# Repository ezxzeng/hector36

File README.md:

# Hector36
## A sub-100×100 mm split keyboard inspired by Totem, without the extra pinky key

left | right | outline
-|-|-
 |  | 

Hector36 is a 36-key split keyboard with a 5×3 layout and 3 thumb keys per half.  
It is designed to stay under **100 mm × 100 mm per PCB**, which makes fabrication much cheaper while still keeping a comfortable, aggressively staggered and splayed layout.

## Features
- Sub-100×100 mm PCB for low fabrication cost
- Split 36-key layout with 3 thumb keys per half
- Reversible PCB
- Diode-less design
- Programmatically generated with Ergogen
- hotswap sockets

## PCB variants

This repo currently contains several board variants:

| Version | Status | Folder | Buildguide |
|---|---|---|---|
| MX | Tested and working | [`routed_pcb/mx`](routed_pcb/mx) | [guide](routed_pcb/mx/README.md#Build-Guide)
| Choc with choc spacing | Fabricated, not yet received or tested | [`routed_pcb/choc_spacing`](routed_pcb/choc_spacing) | tbd
| Choc with mx spacing | Not routed | `routed_pcb/choc` | tbd
| Gateron low profile with mx spacing | Not routed | `routed_pcb/gateron_lp` | tbd

For PCB fabrication through JLCPCB or PCBWay, use the gerbers.zip file inside the corresponding version folder.

## Components

| Part                           | Qty |      Estimated price | Notes                                                          |
| ------------------------------ | --: | -------------------: | -------------------------------------------------------------- |
| PCB                            |   2 |          $3.50 for 5 |                                                                |
| nice!nano or nRF52840          |   2 | $4 each for nRF52840 |  I'm using nRF52840 for cheaper cost |
| Reset switch                   |   2 |        $3.40 for 100 | 3×6×2.5 mm, 2-pin, SMD push button                             |
| Power switch                   |   2 |           $4 for 100 | 7-pin, MSK 12C02                                               |
| Battery                        |   2 |            $15 for 2 | 301230, 3.7 V Li-Po                                            |
| 2P ST PH2.0 right-angle socket |   2 |           $2 for 100 | Optional                                                       |
| Hotswap socket                 |  36 |           $10 for 70 |     also depends on socket type    |
| Switch                         |  36 |                    — |                                                                |
| Keycap                         |  36 |                    — | Some keycaps may need rotated orientation for the Choc version. |
| M3 heat-set insert             |   8 |            $3 for 50 |                                                                |
| M3 screw                       |   8 |            $3 for 50 |                                                                |
| Rubber feet                    |   8 |            $5 for 50 |                                                                |

note that estimated price is from a brief look at aliexpress, and might be higher than what you'll actually have to pay if you buy in higher quantities (especially for batteries)

optional: [socketing the controller](https://docs.splitkb.com/frequently-asked-questions/about-split-keyboards/microcontrollers/sockets), see [this guide](https://www.40percent.club/p/socketing-pro-micro.html) or [this guide](https://docs.splitkb.com/product-guides/aurora-series/build-guide/microcontrollers)

## Firmware
see [zmk module](https://github.com/ezxzeng/zmk-keyboards-hector36)

## Inspiration

- [bgkeeb](https://github.com/sadekbaroudi/bgkeeb)
  - keyboard pcbs under 100mm x 100mm are cheap
- [cheapis](https://github.com/dotleon/cheapis) 
  - sweeps can be rotated for more room and length between the thumb cluster and rest of the keys and still fit within 100mm x 100mm
- [samoklava](https://github.com/soundmonster/samoklava) and [ergogen](https://ergogen.cache.works/) to get keyboard layouts programatically 
- [sweep](https://github.com/davidphilipbarr/Sweep) and [swweeep](https://github.com/sadekbaroudi/sweep36) for form factor and diode-less design
- [totem](https://github.com/GEIGEIGEIST/totem) and [KLOR](https://github.com/GEIGEIGEIST/KLOR)
  - keys layout
  - sandwich case looks really slick and clean, and can also hide the controller parts that will be located under the palm

## Other considerations
- this design does not support LEDs or displays
- [samoklava's](https://github.com/soundmonster/samoklava) auto routing does not really work here
- some keycaps might need to be rotated 90 degrees

## Rendering and generation

### Ergogen:
```bash
ergogen .
```
### Case:
printables: https://www.printables.com/model/1659997-case-for-hector36

onshape [link](https://cad.onshape.com/documents/dab7ead69061981322a5fa82/w/eeec2b07408bf6c3576b55db/e/49101eb28d1b1828dfaa91ca?renderMode=0&uiState=69ce0391edbfc1314134fd9e)

### Get board image renderings:
```bash
export pcb_type="mx"

docker run -v $(pwd):/kikit --entrypoint pcbdraw yaqwsx/kikit:v1.3.0-v7  plot --style style.json routed_pcb/$pcb_type/board.kicad_pcb routed_pcb/$pcb_type/images/board-front.png

docker run -v $(pwd):/kikit --entrypoint pcbdraw yaqwsx/kikit:v1.3.0-v7  plot --style style.json --side back routed_pcb/$pcb_type/board.kicad_pcb routed_pcb/$pcb_type/images/board-back.png
```

## Showcase

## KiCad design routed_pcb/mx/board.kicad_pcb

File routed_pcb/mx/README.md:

left | right | outline
-|-|-
 |  | 

# Build Guide

## 1. PCB
1. Take 2 pcbs and flip them to the **back** side

1. Solder the jumper pads for the controller so that the two sides of the pads can be connected together.

1. Still on the back side, put solder on the pads for the hotswap sockets

1. Melt the solder and press the hotswap sockets down, one side at a time. Use tweezers if that helps.

1. Still on the back side, put down the reset switch and solder it in. Depending on what switch you're using, it might help to bend the pins a bit down so it'll go inside the hole.

1. Flip over to the **front** side. Place the on/off switch and solder it in

1. (Optional) align the JST connectors with the + sign. This may be different from the rectangle drawn on the pcb depending on where you order the right angle JST connectors from, or how the male connector on the battery looks. What's important is that the red wire aligns with the + sign. 

1. Solder the JST connector from the back. Alternatively, solder the battery wires directly.

1. Back on the front side, place the controller **with the components side down**. The markings for which pin is what aligns on the **back** side, not the front. The two pins closest to the USBC port are **empty** and not used. Those are for Battery + and -, which are the same thing as RAW and GND.

optionally, but highly recommended, follow [this](https://www.40percent.club/p/socketing-pro-micro.html) or [this alternative](https://docs.splitkb.com/product-guides/aurora-series/build-guide/microcontrollers) guide on how to socket the controller (see [here](https://docs.splitkb.com/frequently-asked-questions/about-split-keyboards/microcontrollers/sockets) for why you would want to).

1.  The finished PCB should look like this, with the battery slotted under the controller.

1.  Alternatively, if the battery does not fit under the controller, you can also put it on the side like this:

## 2. Case

Before printing, measure the distance from the top of the usbc port to the bottom of the pcb:

If this value is between 7.2mm and 8.2mm, then go ahead and use the STL files available on [printables](https://www.printables.com/model/1659997-case-for-hector36). Otherwise, you can copy and edit the [onshape file](https://cad.onshape.com/documents/dab7ead69061981322a5fa82/w/eeec2b07408bf6c3576b55db/e/49101eb28d1b1828dfaa91ca?renderMode=0&uiState=69db021f7ce9695c3c22be27). Simply modify the `bottom_pcb_to_usbc` variable at the top of the variable table.

1. Print the top half face down, and enable supports:

1. disable support for the bottom part.
2. remove the support for the top half:

1. put in the M3 heat set inserts:

1. put in the switch extender in the orientation shown below

1. put everything together and we're done!

## Firmware
see [zmk module](https://github.com/ezxzeng/zmk-keyboards-hector36)

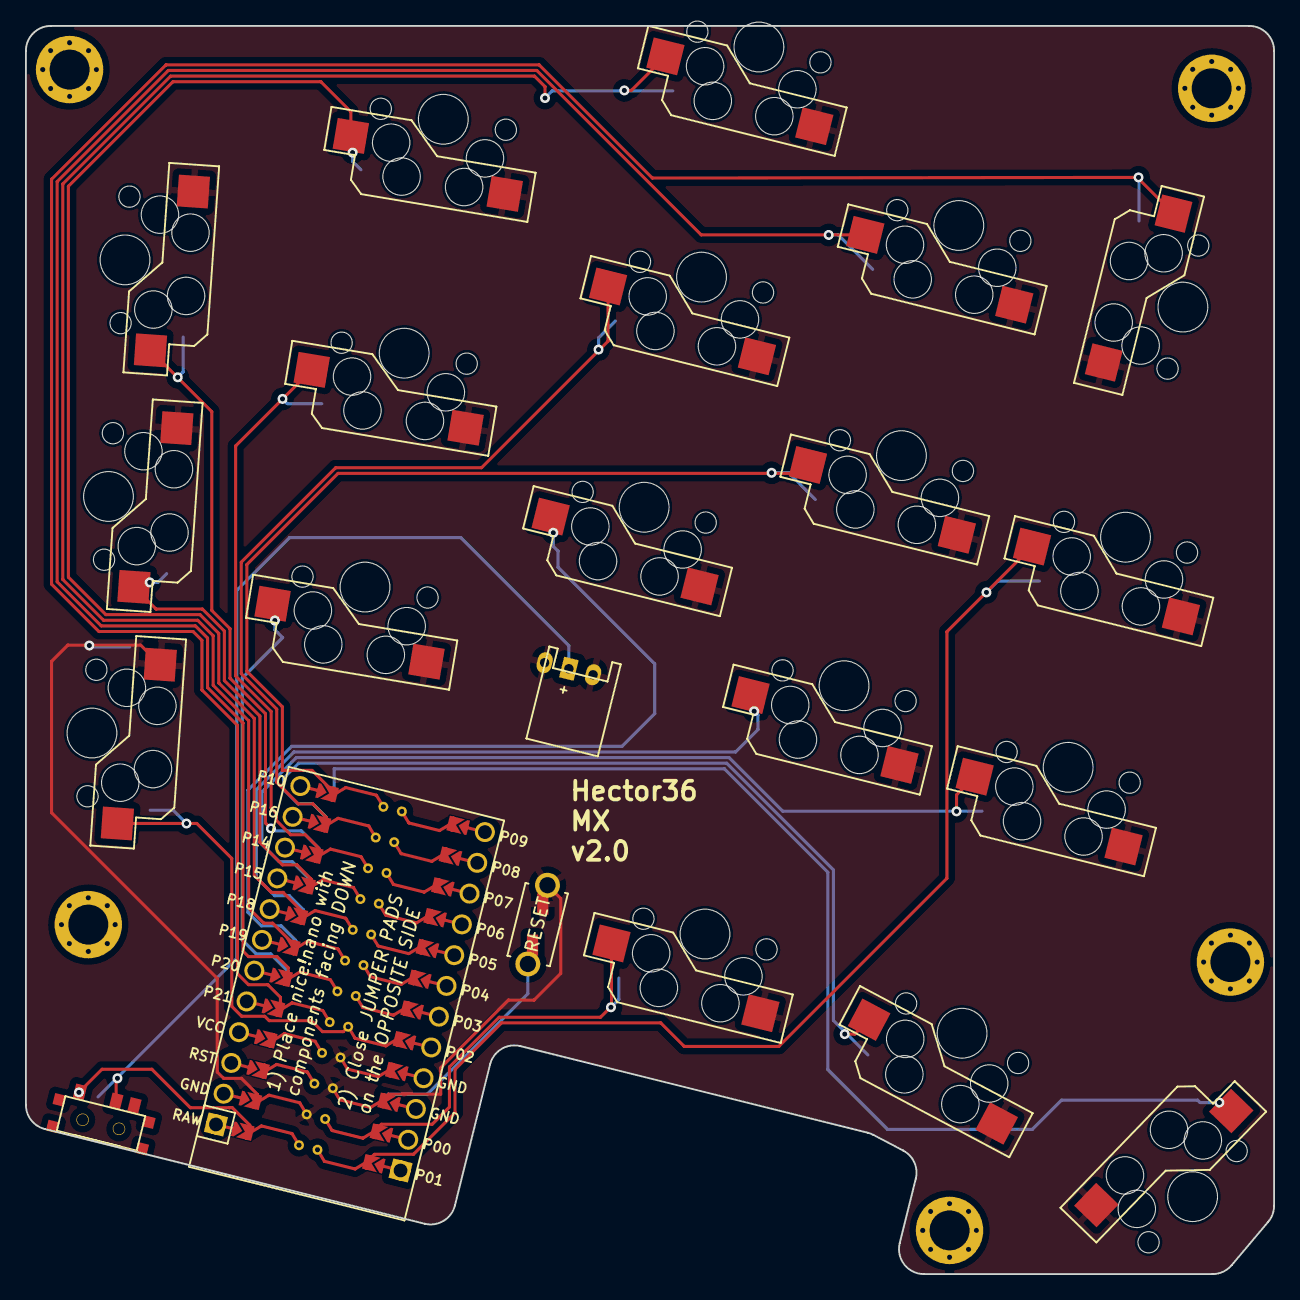
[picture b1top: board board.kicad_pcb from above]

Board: 2 copper layers, 100.0 x 100.0 mm, 28 parts (0 on the bottom side), 22 nets.

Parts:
B1: ResetSW
B2: SW_SPST_B3U-1000P
HOLE1, HOLE2, HOLE3, HOLE4, HOLE5: MountingHole_3.2mm_Pad_Via
JST1: JST_PH_S2B-PH-K_02x2.00mm_Angled
MCU1: ProMicro
SW1, SW2, SW3, SW4, SW5, SW6, SW7, SW8, SW9, SW10, SW11, SW12, SW13, SW14, SW15, SW16, SW17, SW18: key-switches
T1: SPDT_C128955

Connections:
Bplus: JST1.1, T1.2
GND: B1.2, B2.2, JST1.2, MCU1.2, MCU1.21, MCU1.22, SW1.2, SW2.2, SW3.2, SW4.2, SW5.2, SW6.2, SW7.2, SW8.2, SW9.2, SW10.2, SW11.2, SW12.2, SW13.2, SW14.2, SW15.2, SW16.2, SW17.2, SW18.2
RAW: MCU1.1, T1.1
RST: B1.1, B2.1, MCU1.3
matrix_index_bottom: MCU1.17, SW10.1
matrix_index_home: MCU1.12, SW11.1
matrix_index_top: MCU1.6, SW12.1
matrix_inner_bottom: MCU1.16, SW13.1
matrix_inner_home: MCU1.24, SW14.1
matrix_inner_top: MCU1.5, SW15.1
matrix_middle_bottom: MCU1.18, SW7.1
matrix_middle_home: MCU1.11, SW8.1
matrix_middle_top: MCU1.7, SW9.1
matrix_pinky_bottom: MCU1.20, SW1.1
matrix_pinky_home: MCU1.9, SW2.1
matrix_pinky_top: MCU1.15, SW3.1
matrix_ring_bottom: MCU1.19, SW4.1
matrix_ring_home: MCU1.10, SW5.1
matrix_ring_top: MCU1.8, SW6.1
thumb_inner: MCU1.23, SW16.1
thumb_reachy: MCU1.13, SW18.1
thumb_tucky: MCU1.14, SW17.1

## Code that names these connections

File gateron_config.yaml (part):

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          shift: [center_x+mcu_x, center_y+mcu_y]
          rotate: mcu_rot
        params:
          P7: matrix_pinky_top
          P18: matrix_ring_top
          P19: matrix_middle_top
          P20: matrix_index_top
          P21: matrix_inner_top
          P15: matrix_pinky_home
          P14: matrix_ring_home
          P16: matrix_middle_home
          P10: matrix_index_home
          P1: matrix_inner_home
          P2: matrix_pinky_bottom
          P3: matrix_ring_bottom
          P4: matrix_middle_bottom
          P5: matrix_index_bottom
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
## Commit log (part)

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2026-03-14 add footprints submodule
2026-03-15 routed pcb
2026-03-15 Fix typo in project name from 'Hecto36' to 'Hector36'
2026-04-02 added case, images
2026-04-06 updated list of materials, choc variant
2026-04-12 added build guide for mx version
2026-04-12 removed photo reference that doesn't exist
2026-04-12 added socketing the controller to optional components
2026-04-13 added link to zmk module
2026-05-09 choc v1.1 and mx v1.2
2026-05-09 battery cuttout in mx config for v1.2
2026-05-10 choc spacing v1.2 with all pads on bottom of key
2026-05-10 cleaned up config file, routed gateron pcb
2026-05-10 updated images
2026-05-10 cleaned up text on mx, routed choc mx spacing
2026-05-11 modified mx switch orientation to be the same as all the other mx spacing versions
